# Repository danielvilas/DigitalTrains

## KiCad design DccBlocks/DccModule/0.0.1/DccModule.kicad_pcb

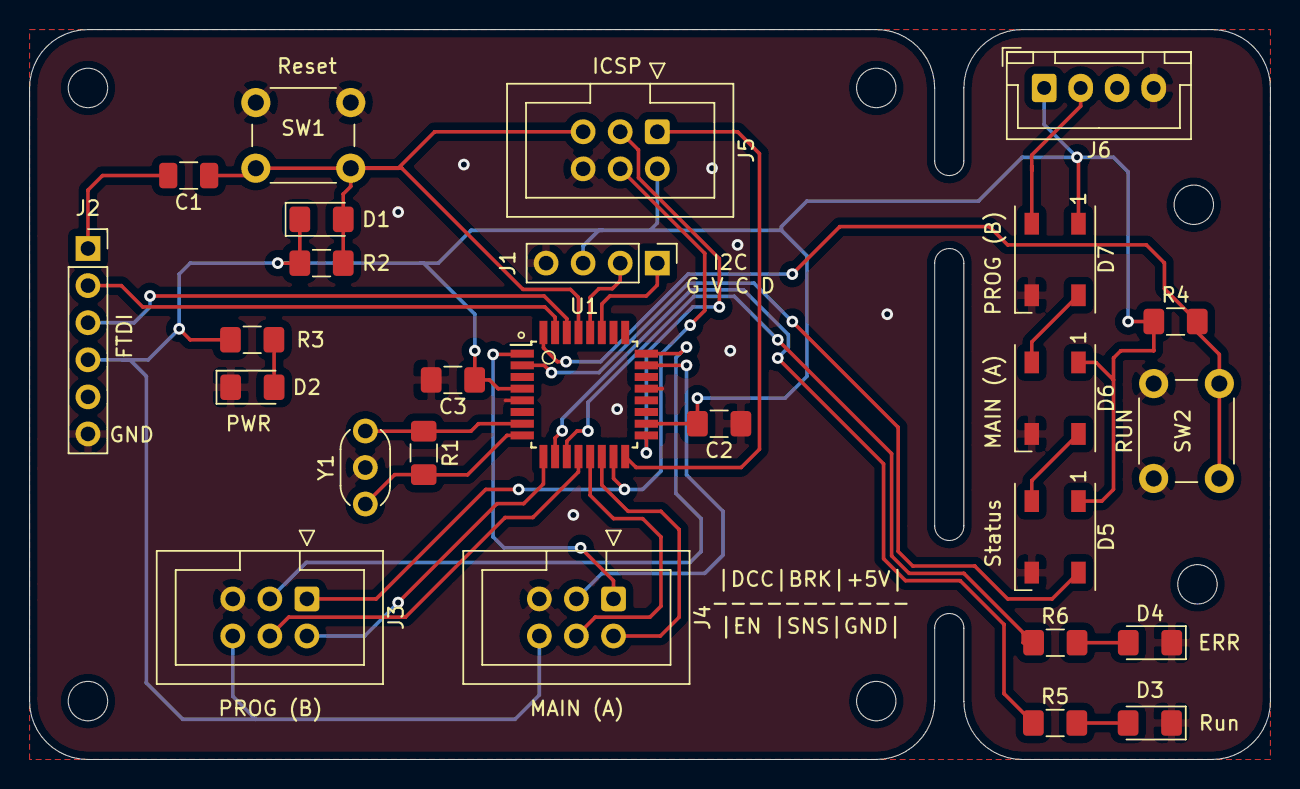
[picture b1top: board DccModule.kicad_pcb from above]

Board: 2 copper layers, 85.0 x 50.0 mm, 32 parts (0 on the bottom side), 30 nets.

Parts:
C1: 100nf; C_1206_3216Metric
C2, C3: 100nF; C_1206_3216Metric_Pad1.42x1.75mm_HandSolder
D1: CD1206-S01575; D_1206_3216Metric_Pad1.42x1.75mm_HandSolder
D2, D3: LED_GREEN; LED_1206_3216Metric_Pad1.42x1.75mm_HandSolder
D4: LED_RED; LED_1206_3216Metric_Pad1.42x1.75mm_HandSolder
D5, D6, D7: WS2812B; LED_WS2812B_PLCC4_5.0x5.0mm_P3.2mm
H1, H2, H3, H4, H5, H6: MountingHole; MountingHole_2.7mm_M2.5
J1: Conn_01x04; PinHeader_1x04_P2.54mm_Vertical
J2: Conn_01x06; PinSocket_1x06_P2.54mm_Vertical
J3, J4: Conn_02x03_Odd_Even; IDC-Header_2x03_P2.54mm_Vertical
J5: ICSP; IDC-Header_2x03_P2.54mm_Vertical
J6: Conn_01x04; JST_XH_B4B-XH-A_1x04_P2.50mm_Vertical
R1: 1M; R_1206_3216Metric_Pad1.42x1.75mm_HandSolder
R2: 10K; R_1206_3216Metric_Pad1.42x1.75mm_HandSolder
R3, R4, R5, R6: 1K; R_1206_3216Metric_Pad1.42x1.75mm_HandSolder
SW1, SW2: SW_Push; SW_PUSH_6mm_H4.3mm
U1: ATmega328PB-AU; TQFP-32_7x7mm_P0.8mm
Y1: CSTLS16M0X53-A0; Resonator_muRata_CSTLSxxxX-3Pin_W5.5mm_H3.0mm

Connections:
+5V: C2.2, C3.1, D1.1, D5.1, D6.1, D7.1, J1.3, J2.4, J3.6, J4.6, J5.2, J6.1, R2.1, R3.1, R4.1, U1.4, U1.18
/Arduino/PB4_ap_12_miso: J5.1, U1.16
/Arduino/PB5_ap_13_sck: J5.3, U1.17
/Arduino/PC6_ap_rst: C1.1, D1.2, J5.5, R2.2, SW1.2, U1.29
/Brake_A: J4.4, U1.13
/Brake_B: J3.4, U1.12
/DCC_A: J4.2, U1.14
/DCC_B: J3.2, U1.9
/DTR: C1.2, J2.1
/EN_A: J4.1, U1.1
/EN_B: J3.1, J5.4, U1.15
/Error: R6.1, U1.11
/NeoPixel: D5.4, U1.2
/RX: J2.2, U1.31
/Run: R5.1, U1.10
/SCL: J1.2, U1.28
/SDA: J1.1, U1.27
/Sns_A: J4.3, U1.23
/Sns_B: J3.3, U1.24
/TX: J2.3, U1.30
/btnRun: R4.2, SW2.2, U1.32
GND: C2.1, C3.2, D2.1, D3.1, D4.1, D5.3, D6.3, D7.3, J1.4, J2.6, J3.5, J4.5, J5.6, J6.4, SW1.1, SW2.1, U1.5, U1.21, Y1.2
unnamed: D2.2, R3.2
unnamed: D3.2, R5.2
unnamed: D4.2, R6.2
unnamed: D5.2, D6.4
unnamed: D6.2, D7.4
unnamed: D7.2, J6.2
unnamed: R1.1, U1.7, Y1.3
unnamed: R1.2, U1.8, Y1.1

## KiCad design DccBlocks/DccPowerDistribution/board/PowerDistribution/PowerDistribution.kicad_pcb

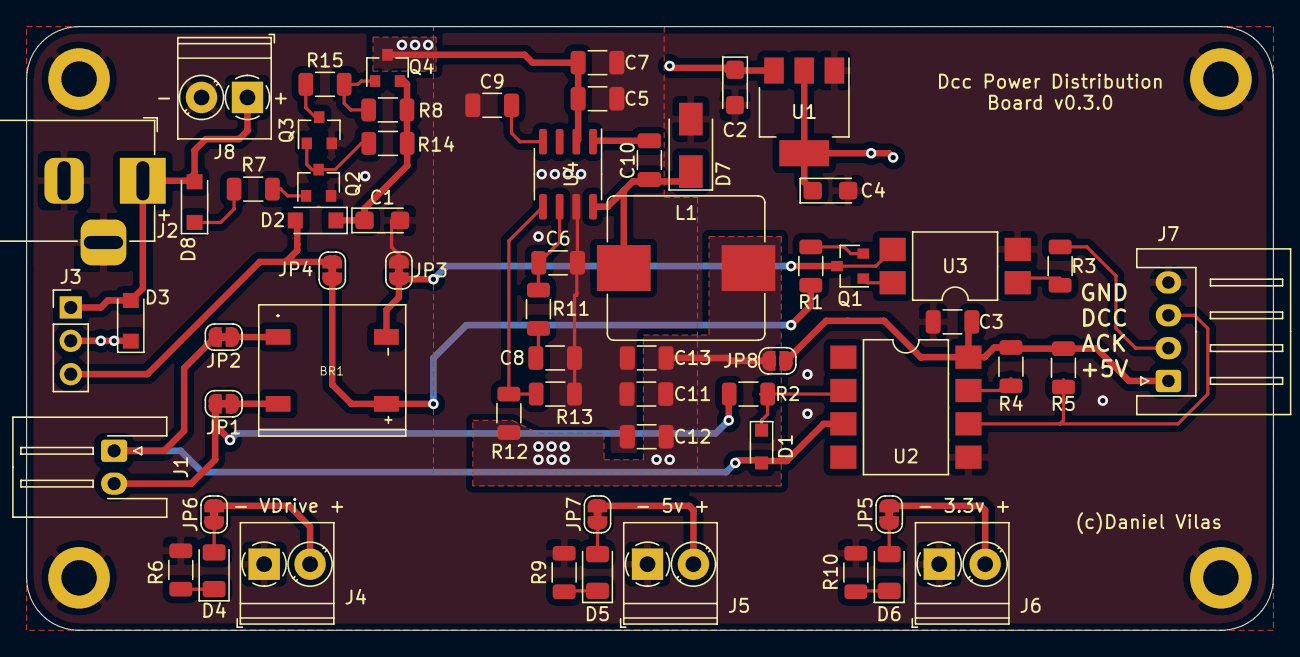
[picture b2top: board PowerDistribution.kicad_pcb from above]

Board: 4 copper layers, 95.0 x 46.0 mm, 66 parts (0 on the bottom side), 38 nets.

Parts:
BR1: DB107S; DIOB_DB107S
C1, C2, C4: 10uf; CP_EIA-3216-18_Kemet-A
C3: 10uf; C_1206_3216Metric
C5, C7, C11, C12, C13: 10uf 2m; C_1206_3216Metric
C6: 10pf; C_1206_3216Metric
C8: 5.6nf; C_1206_3216Metric
C9: 8.2nf; C_1206_3216Metric
C10: 100nf 1m; C_1206_3216Metric
D1: 1N4148; D_SOD-323_HandSoldering
D2, D3, D8: GS1510FL; D_SOD-123FL
D4, D5, D6: LED; LED_1206_3216Metric
D7: SS24A+; D_SMA
H1, H2, H3, H4: MountingHole_Pad; MountingHole_2.7mm_M2.5_DIN965_Pad
J1: Conn_01x02; JST_XH_S2B-XH-A-1_1x02_P2.50mm_Horizontal
J2: Conn_01x02; BarrelJack_Horizontal
J3: Conn_01x03; PinHeader_1x03_P2.54mm_Vertical
J4, J5, J6, J8: Conn_01x02; TerminalBlock_Phoenix_PT-1,5-2-3.5-H_1x02_P3.50mm_Horizontal
J7: Conn_01x04; JST_XH_S4B-XH-A_1x04_P2.50mm_Horizontal
JP1, JP2, JP3, JP4: Jumper_NC; SolderJumper-2_P1.3mm_Bridged_RoundedPad1.0x1.5mm
JP5, JP6, JP7: Jumper_2_Bridged; SolderJumper-2_P1.3mm_Bridged_RoundedPad1.0x1.5mm
JP8: SolderJumper_2_Open; SolderJumper-2_P1.3mm_Open_RoundedPad1.0x1.5mm
L1: 22uH 75mO; L_Bourns_SRP1035
Q1: BC857; SOT-23
Q2: BC817; SOT-23
Q3: 2N7002; SOT-23
Q4: BSS308; SOT-23
R1, R10: 100; R_1206_3216Metric
R2: 3k; R_1206_3216Metric
R3: 1K; R_1206_3216Metric
R4, R5: 10K; R_1206_3216Metric
R6: 900; R_1206_3216Metric
R7, R8, R14, R15: 100K; R_1206_3216Metric
R9: 200; R_1206_3216Metric
R11: 5.62K; R_1206_3216Metric
R12: 10.2K; R_1206_3216Metric
R13: 1.96K; R_1206_3216Metric
U1: AMS1117-3.3; SOT-223-3_TabPin2
U2: 6N137S1; SMDIP-8_W9.53mm
U3: PC817; SMDIP-4_W9.53mm
U4: TPS54331D; SOIC-8_3.9x4.9mm_P1.27mm

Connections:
+3V3: C4.1, J6.2, JP5.2, U1.2
+5V: C2.1, C11.1, C12.1, C13.1, J5.2, JP7.2, JP8.1, L1.2, R12.1, U1.3
/5V_iFace: C3.1, J7.1, JP8.2, R4.2, R5.2, U2.8
/Dcc Interface/DccP+: BR1.+, JP4.1, R1.2
/Dcc Interface/DccP-: BR1.-, JP3.1, Q1.3, U3.3
/Dcc Interface/DccPower: D2.2, J3.3, JP4.2
/Dcc Interface/J: J1.2, JP1.2, R2.2
/Dcc Interface/J_ACK: BR1.~, JP1.1
/Dcc Interface/K: D1.2, J1.1, JP2.2, U2.3
/Dcc Interface/K_ACK: BR1.~., JP2.1
/Power Distribution/Vin: D3.2, D8.2, J2.1, J3.1, J8.1
/Power Distribution/_BOOT: C10.1, U4.1
/Power Distribution/_DccVinP: C1.1, D2.1, Q4.2, R8.1, R14.1
/Power Distribution/_PH: C10.2, D7.1, L1.1, U4.8
/_ack: J7.2, R3.1
/_dcc: J7.3, R5.1, U2.6
GND: C1.2, C2.2, C3.2, C4.2, C5.2, C6.2, C7.2, C8.2, C9.2, C11.2, C12.2, C13.2, D7.2, H1.1, H2.1, H3.1, H4.1, J2.2, J2.3, J4.1, J5.1, J6.1, J7.4, J8.2, JP3.2, Q2.2, Q3.2, R6.2, R9.2, R10.2, R13.2, U1.1, U2.5, U3.2, U4.7
unnamed: C6.1, R11.1, U4.6
unnamed: C8.1, R11.2
unnamed: C9.1, U4.4
unnamed: D1.1, R2.1, U2.2
unnamed: D4.1, R6.1
unnamed: D4.2, JP6.1
unnamed: D5.1, R9.1
unnamed: D5.2, JP7.1
unnamed: D6.1, R10.1
unnamed: D6.2, JP5.1
unnamed: D8.1, R7.2
unnamed: Q1.1, U3.4
unnamed: Q1.2, R1.1
unnamed: Q2.1, R7.1
unnamed: Q2.3, Q3.1, R14.2
unnamed: Q3.3, R15.1
unnamed: Q4.1, R8.2, R15.2
unnamed: R3.2, U3.1
unnamed: R4.1, U2.7
unnamed: R12.2, R13.1, U4.5
Vdrive: C5.1, C7.1, D3.1, J3.2, J4.2, JP6.2, Q4.3, U4.2

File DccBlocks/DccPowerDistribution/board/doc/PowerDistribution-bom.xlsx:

|  | Bill of Materials
 |  | Schematic: | PowerDistribution | Component Groups: | 40
 |  | Variant: | default | Component Count: | 64 (48 SMD/ 9 THT)
 |  | Revision: | v1.0.0-RC2 | Fitted Components: | 64 (48 SMD/ 9 THT)
 |  | Date: | 2021-11-09 | Number of PCBs: | 1
 |  | KiCad Version: | 6.0.7+dfsg-1build1 | Total Components: | 64
Row | Description | Part | References | Value | Footprint | Quantity Per PCB | Status | Datasheet | Mouser# | MNF# | LCSC# | Farnell# | Tolerance | MANUFACTURER
1 | DBS107 Bridge Rectifier | DB107S | BR1 | KMB26STR | DIOB_KMB26S | 1 |  | http://www.smc-diodes.com/propdf/KMB22S%20THRU%20KMB225S%20N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 |  | KMB26STR |  |  |  | Rectron Semiconductor
2 | Unpolarized capacitor | C | C6 | 10pf | C_1206_3216Metric | 1 |  | ~ |  | 1206N100J500CT |  | 2497123
3 | Unpolarized capacitor | C | C8 | 5.6nf | C_1206_3216Metric | 1 |  | ~ |  | MC1206B562K500CT |  | 1759347
4 | Unpolarized capacitor | C | C9 | 8.2nf | C_1206_3216Metric | 1 |  | ~ |  | MC1206B822K500CT |  | 1759349
5 | Unpolarized capacitor | C | C10 | 100nf | C_1206_3216Metric | 1 |  | ~ |  | C1206C104M5RACTU |  | 2581103 | 1mO
6 | Polarized capacitor | C_Polarized | C1 C2 C4 | 10uf | CP_EIA-3216-18_Kemet-A | 3 |  | ~ | 80-T494A106M020 | T494A106M020AT | C7171 |  | ~
7 | Unpolarized capacitor | C | C5 C7 C11 C12 C13 | 10uf | C_1206_3216Metric | 5 |  | ~ | 187-CL31A106KPHNNNE | CL31A106KPHNNNE |  |  | 2mO
8 | Unpolarized capacitor | C | C3 | 10uf | C_1206_3216Metric | 1 |  | ~ |  |  | C15850 | 2803344 | ~
9 | Polarized capacitor | C_Polarized | C14 C15 C16 | 100uf | CP_Elec_6.3x7.7 | 3 |  | ~ |  | 865060445005
10 | 100V 0.15A standard switching diode, DO-35 | 1N4148 | D1 | 1N4148 | D_SOD-323_HandSoldering | 1 |  | https://assets.nexperia.com/documents/data-sheet/1N4148_1N4448.pdf | 833-1N4148WX-TP | 1N4148WX-TP | C2128
11 | Diode | D | D2 D3 D8 | GS1510FL | D_SOD-123FL | 3 |  | ~ | 241-GS1510FLR100001 | GS1510FL_R1_00001
12 | Light emitting diode | LED | D4 D5 D6 | LED | LED_1206_3216Metric | 3 |  | ~
13 | Schottky diode | D_Schottky | D7 | SS24A+ | D_SMA | 1 |  | ~ |  | SS24A+ |  | 2748189
14 | DC Barrel Jack with an internal switch | Barrel_Jack_Switch | J2 | DcJackSW | BarrelJack_Horizontal | 1 |  | ~ | 806-KLDX-0202-A | KLDX-0202-A
15 | Generic connector, single row, 01x02, script generated (kicad-library-utils/sch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 | Conn_01x02 | J1 | JST_01x02 | JST_XH_S2B-XH-A-1_1x02_P2.50mm_Horizontal | 1 |  | ~
16 | Generic connector, single row, 01x04, script generated (kicad-library-utils/sch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 | Conn_01x04 | J7 | JST_01x04 | JST_XH_S4B-XH-A_1x04_P2.50mm_Horizontal | 1 |  | ~
17 | Generic connector, single row, 01x03, script generated (kicad-library-utils/sch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 | Conn_01x03 | J3 | Pin_01x03 | PinHeader_1x03_P2.54mm_Vertical | 1 |  | ~ |  | 1776275-2 |  | 1098611
18 | Generic connector, single row, 01x02, script generated (kicad-library-utils/sch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 | Conn_01x02 | J8 | Screw_01x02_Black | TerminalBlock_Phoenix_PT-1,5-2-3.5-H_1x02_P3.50mm_Horizontal | 1 |  | ~ |  | CTB3051/2BK |  | 3882615
19 | Generic connector, single row, 01x02, script generated (kicad-library-utils/sch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 | Conn_01x02 | J4 J5 J6 | Screw_01x02_blue | TerminalBlock_Phoenix_PT-1,5-2-3.5-H_1x02_P3.50mm_Horizontal | 3 |  | ~ |  | 1776275-2 |  | 1098611
20 | Jumper, 2-pole, closed/bridged | Jumper_2_Bridged | JP5 JP6 JP7 | Jumper_2_Bridged | SolderJumper-2_P1.3mm_Bridged_RoundedPad1.0x1.5mm | 3 |  | ~
21 | Jumper, 2-pole, closed/bridged | Jumper_2_Bridged | JP1 JP2 JP3 JP4 | Jumper_NC | SolderJumper-2_P1.3mm_Bridged_RoundedPad1.0x1.5mm | 4 |  | ~
22 | Inductor | L | L1 | 22uH | L_Bourns_SRP1035 | 1 |  | ~ |  | SRP1038A-220M |  | 2434023 | 75mO
23 | 0.115A Id, 60V Vds, N-Channel MOSFET, SOT-23 | 2N7002 | Q3 | 2N7002 | SOT-23 | 1 |  | https://www.onsemi.com/pub/Collateral/NDS7002A-D.PDF
24 | 0.8A Ic, 45V Vce, NPN Transistor, SOT-23 | BC817 | Q2 | BC817 | SOT-23 | 1 |  | https://www.onsemi.com/pub/Collateral/BC818-D.pdf | 771-BC817-25-T/R | BC817-25,215
25 | PNP transistor, base/emitter/collector | Q_PNP_BEC | Q1 | BC857 | SOT-23 | 1 |  | http://www.fairchildsemi.com/ds/BC/BC557.pdf | 771-BC857C235 | BC857C,235 | C8326
26 | P-MOSFET transistor, gate/source/drain | Q_PMOS_GSD | Q4 | BSS308 | SOT-23 | 1 |  | ~ | 726-BSS308PEH6327 | BSS308PE H6327
27 | Resistor | R | R1 R10 | 100 | R_1206_3216Metric | 2 |  | ~ | 603-AC1206FR-10100RL | AC1206FR-10100RL | C17901
28 | Resistor | R | R9 | 200 | R_1206_3216Metric | 1 |  | ~ | 603-RC1206FR-07200RL | RC1206FR-07200RL
29 | Resistor | R | R6 | 900 | R_1206_3216Metric | 1 |  | ~ | 652-CR1206FX-9090ELF | CR1206-FX-9090ELF
30 | Resistor | R | R3 | 1K | R_1206_3216Metric | 1 |  | ~ | 652-CR1206FX-1001ELF | CR1206-FX-1001ELF | C17513
31 | Resistor | R | R13 | 1.96K | R_1206_3216Metric | 1 |  | ~ |  | ERJ8ENF1961V |  | 2307494
32 | Resistor | R | R2 | 3k | R_1206_3216Metric | 1 |  | ~ |  |  | C17661
33 | Resistor | R | R11 | 5.62K | R_1206_3216Metric | 1 |  | ~ |  | ERJ8ENF5621V |  | 2695169
34 | Resistor | R | R4 R5 | 10K | R_1206_3216Metric | 2 |  | ~ | 652-CR1206FX-1002ELF | CR1206-FX-1002ELF | C17414
35 | Resistor | R | R12 | 10.2K | R_1206_3216Metric | 1 |  | ~ |  | ERJ8ENF1022V |  | 2307301
36 | Resistor | R | R7 R8 R14 R15 | 100K | R_1206_3216Metric | 4 |  | ~
37 | Single High Speed LSTTL/TTL Compatible Optocoupler with enable, dV/dt 1000/us, 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 | 6N137 | U2 | 6N137S1 | SMDIP-8_W9.53mm | 1 |  | https://docs.broadcom.com/docs/AV02-0940EN | 512-6N137SDM | 6N137SDM | C110020
38 | 1A Low Dropout regulator, positive, 3.3V fixed output, SOT-223 | AMS1117-3.3 | U1 | AMS1117-3.3 | SOT-223-3_TabPin2 | 1 |  | http://www.advanced-monolithic.com/pdf/ds1117.pdf | 863-NCP1117LPST33T3G | NCP1117LPST33T3G | C6186
39 | DC Optocoupler, Vce 35V, CTR 50-300%, DIP-4 | PC817 | U3 | PC817 | SMDIP-4_W9.53mm | 1 |  | http://www.soselectronic.cz/a_info/resource/d/pc817.pdf | 852-PC817X2NIP1B | PC817X2NIP1B | C106900
40 | Buck Converter | TPS54331D | U4 | TPS54331D | SOIC-8_3.9x4.9mm_P1.27mm | 1 |  |  |  | TPS54331D |  | 1645383

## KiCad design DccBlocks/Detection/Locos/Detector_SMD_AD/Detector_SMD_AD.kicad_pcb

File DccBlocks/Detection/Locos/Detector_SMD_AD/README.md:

# SMD Analogic and Digital
Train on Track Detector by current measure. This module has digital output and an analogic output proportional to the current usage.

## Changelog
### 0.0.1
* Initial Version
### 0.0.2
* [x] Silk Screen with descriptions
* [x] Changed components to 1206

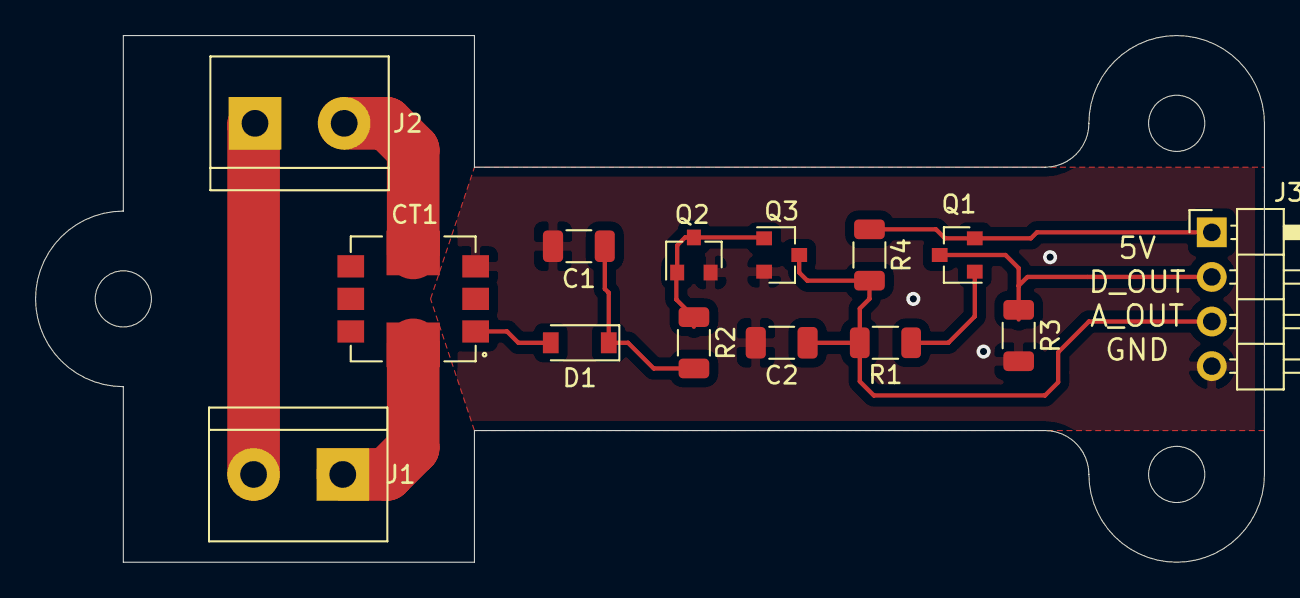
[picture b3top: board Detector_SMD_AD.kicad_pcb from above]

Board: 2 copper layers, 70.0 x 30.0 mm, 17 parts (0 on the bottom side), 11 nets.

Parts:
C1, C2: 0.1u; C_1206_3216Metric
CT1: Murata5300; Murata53000
D1: 1N4148W; D_SOD-123
H1, H2, H3: MountingHole; MountingHole_3.2mm_M3
J1, J2: Conn_01x02; TerminalBlock_bornier-2_P5.08mm
J3: Conn_01x04; PinHeader_1x04_P2.54mm_Horizontal
Q1: BC807; SOT-23
Q2, Q3: BC849; SOT-23
R1, R2: 1K; R_1206_3216Metric
R3, R4: 10K; R_1206_3216Metric

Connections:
+5V: J3.1, Q1.2, R4.1
/A_Out: C2.1, J3.3, Q3.3, R1.2, R4.2
/DCC_J: J1.2, J2.1
/DCC_K_1: CT1.8, J1.1
/DCC_K_2: CT1.7, J2.2
/D_Out: J3.2, Q1.3, R3.1
GND: C1.2, C2.2, CT1.3, J3.4, Q2.2, Q3.2, R3.2
unnamed: C1.1, D1.1, R2.2
unnamed: CT1.1, D1.2
unnamed: Q1.1, R1.1
unnamed: Q2.1, Q2.3, Q3.1, R2.1

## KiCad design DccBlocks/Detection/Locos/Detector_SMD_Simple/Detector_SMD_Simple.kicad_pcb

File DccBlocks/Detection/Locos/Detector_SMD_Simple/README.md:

# SMD Simple
Train on Track Detector by current measure. This module only has digital output, when the current is the minimum the output will be '0' if no current output will be '1'

## Changelog
### 0.0.1
* Initial Version
### 0.0.2
* [x] Silk Screen with descriptions
* [x] Changed components to 1206

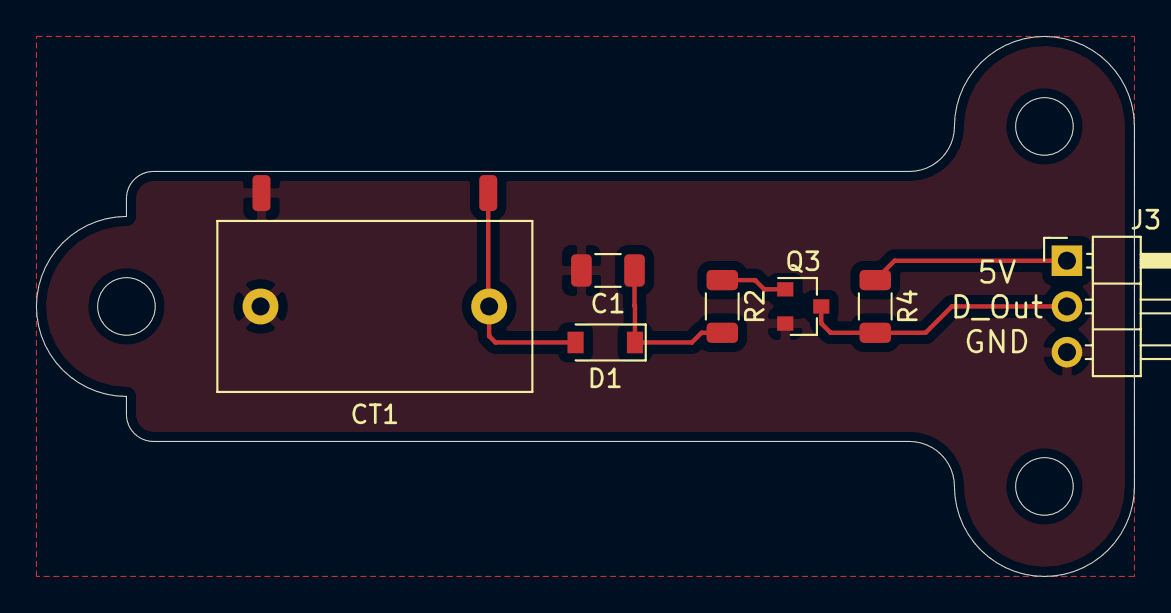
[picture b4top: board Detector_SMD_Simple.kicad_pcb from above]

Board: 2 copper layers, 61.0 x 30.0 mm, 12 parts (0 on the bottom side), 6 nets.

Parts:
C1: 0.1u; C_1206_3216Metric
CT1: 56050C; Murata5600
D1: 1N4148W; D_SOD-123
H1, H2, H3: MountingHole; MountingHole_3.2mm_M3
J1, J2: Conn_01x01; SolderWirePad_1x01_SMD_1x2mm
J3: Conn_01x03; PinHeader_1x03_P2.54mm_Horizontal
Q3: BC849; SOT-23
R2: 1K; R_1206_3216Metric
R4: 10K; R_1206_3216Metric

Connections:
+5V: J3.1, R4.1
/Free_Out: J3.2, Q3.3, R4.2
GND: C1.2, CT1.1, J2.1, J3.3, Q3.2
unnamed: C1.1, D1.1, R2.2
unnamed: CT1.2, D1.2, J1.1
unnamed: Q3.1, R2.1

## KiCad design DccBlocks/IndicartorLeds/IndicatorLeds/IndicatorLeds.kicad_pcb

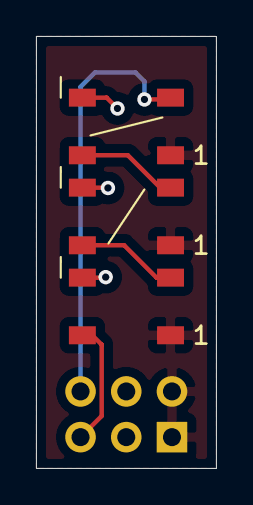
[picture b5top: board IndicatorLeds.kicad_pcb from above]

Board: 2 copper layers, 10.0 x 24.0 mm, 4 parts (1 on the bottom side), 6 nets.

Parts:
D1, D2, D3: WS2812B; LED_WS2812B_PLCC4_5.0x5.0mm_P3.2mm
J1: Conn_02x03_Odd_Even; PinHeader_2x03_P2.54mm_Vertical

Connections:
/Din: D1.4, J1.5
/Dout: D3.2, J1.6
GND: D1.3, D2.3, D3.3, J1.3, J1.4
unnamed: D1.2, D2.4
unnamed: D2.2, D3.4
VCC: D1.1, D2.1, D3.1, J1.1, J1.2
